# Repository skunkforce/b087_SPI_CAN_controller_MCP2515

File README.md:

# edgy_board number b087
This design is part of the [edgy board project](https://github.com/skunkforce/edgy_boards). 

# getting started
This repository uses submodules. After cloning use the command 

```$ git submodule update --init --recursive```

to pull the submodules before opening the project with kicad. 

# Tests
Tests can be found in [TESTS.md](TESTS.md)

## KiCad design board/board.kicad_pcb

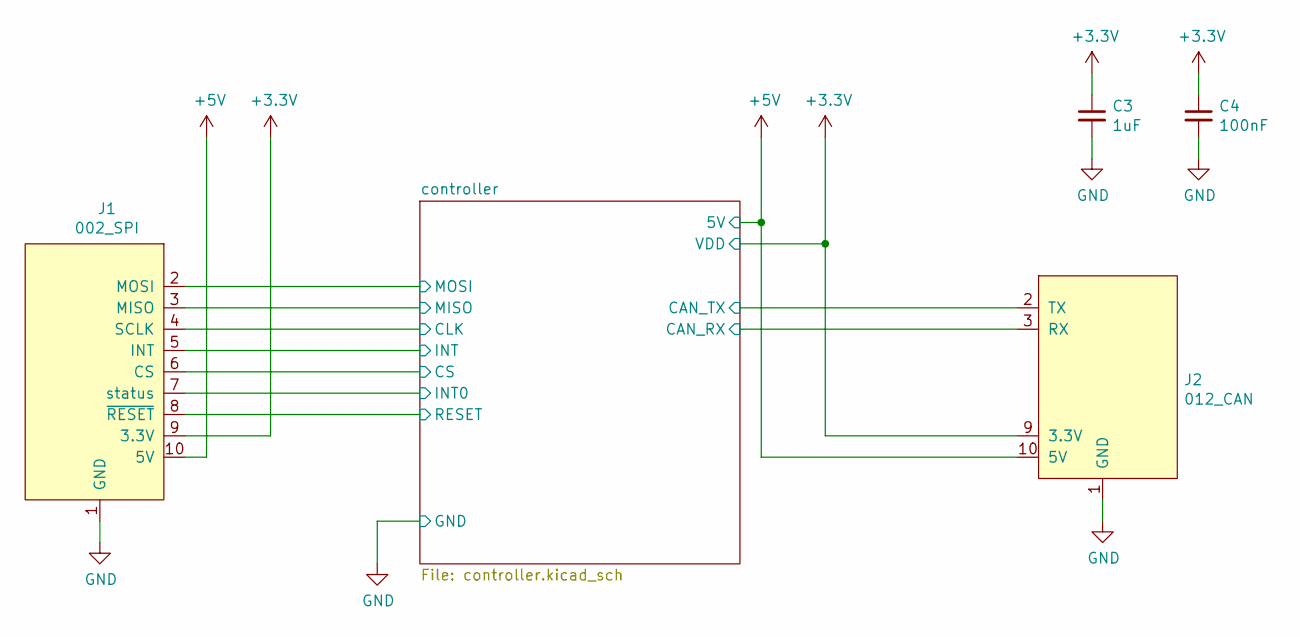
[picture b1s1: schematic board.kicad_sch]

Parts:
C3: 1uF; C_0603_1608Metric; Voltage 6.3V; lcsc C15849
C4: 100nF; C_0603_1608Metric; Voltage 6.3V; lcsc C14663
J1: 002_SPI; on_edge_2x05_device
J2: 012_CAN; on_edge_2x05_host

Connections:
+3.3V: C3.1, C4.1, J1.9 (3.3V), J2.9 (3.3V); also elsewhere on the board
+5V: J1.10 (5V), J2.10 (5V)
/controller/CAN_RX: J2.3 (RX); also elsewhere on the board
/controller/CAN_TX: J2.2 (TX); also elsewhere on the board
/controller/CLK: J1.4 (SCLK); also elsewhere on the board
/controller/CS: J1.6 (CS); also elsewhere on the board
/controller/INT: J1.5 (INT); also elsewhere on the board
/controller/INT0: J1.7 (status); also elsewhere on the board
/controller/MISO: J1.3 (MISO); also elsewhere on the board
/controller/MOSI: J1.2 (MOSI); also elsewhere on the board
/controller/RESET: J1.8 (~RESET); also elsewhere on the board
GND: C3.2, C4.2, J1.1 (GND), J2.1 (GND); also elsewhere on the board

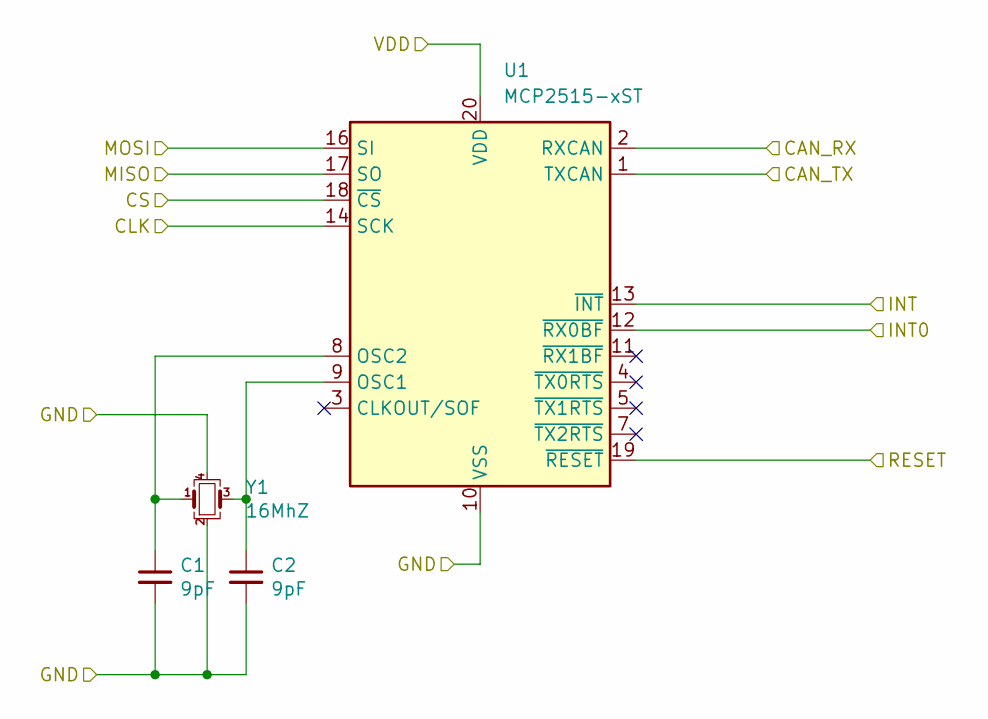
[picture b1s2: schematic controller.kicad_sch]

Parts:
C1, C2: 9pF; C_0603_1608Metric; Voltage 6.3V; lcsc C1634
U1: MCP2515-xST; TSSOP-20_4.4x6.5mm_P0.65mm; lcsc C185941
Y1: 16MhZ; Crystal_SMD_Abracon_ABM8G-4Pin_3.2x2.5mm; MPN ECS-200-18-33-JGN-TR; lcsc C13738

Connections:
+3.3V: U1.20 (VDD); also elsewhere on the board
/controller/CAN_RX: U1.2 (RXCAN); also elsewhere on the board
/controller/CAN_TX: U1.1 (TXCAN); also elsewhere on the board
/controller/CLK: U1.14 (SCK); also elsewhere on the board
/controller/CS: U1.18 (~CS); also elsewhere on the board
/controller/INT: U1.13 (~INT); also elsewhere on the board
/controller/INT0: U1.12 (~RX0BF); also elsewhere on the board
/controller/MISO: U1.17 (SO); also elsewhere on the board
/controller/MOSI: U1.16 (SI); also elsewhere on the board
/controller/RESET: U1.19 (~RESET); also elsewhere on the board
GND: C1.2, C2.2, U1.10 (VSS), Y1.2, Y1.4; also elsewhere on the board
unnamed: C2.1, U1.9 (OSC1), Y1.3
unnamed: C1.1, U1.8 (OSC2), Y1.1

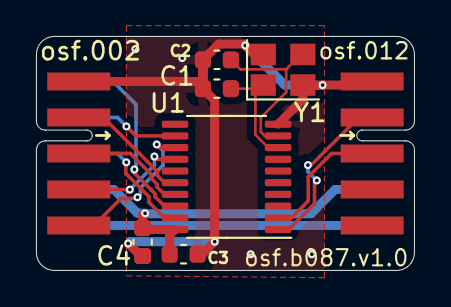
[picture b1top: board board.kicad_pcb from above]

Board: 2 copper layers, 21.0 x 13.0 mm, 8 parts (0 on the bottom side), 14 nets.

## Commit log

2024-06-28 imported legacy version
2024-06-28 updated to kicad 8.0 and 20pin tssop
2024-06-29 added lcsc part numbers
